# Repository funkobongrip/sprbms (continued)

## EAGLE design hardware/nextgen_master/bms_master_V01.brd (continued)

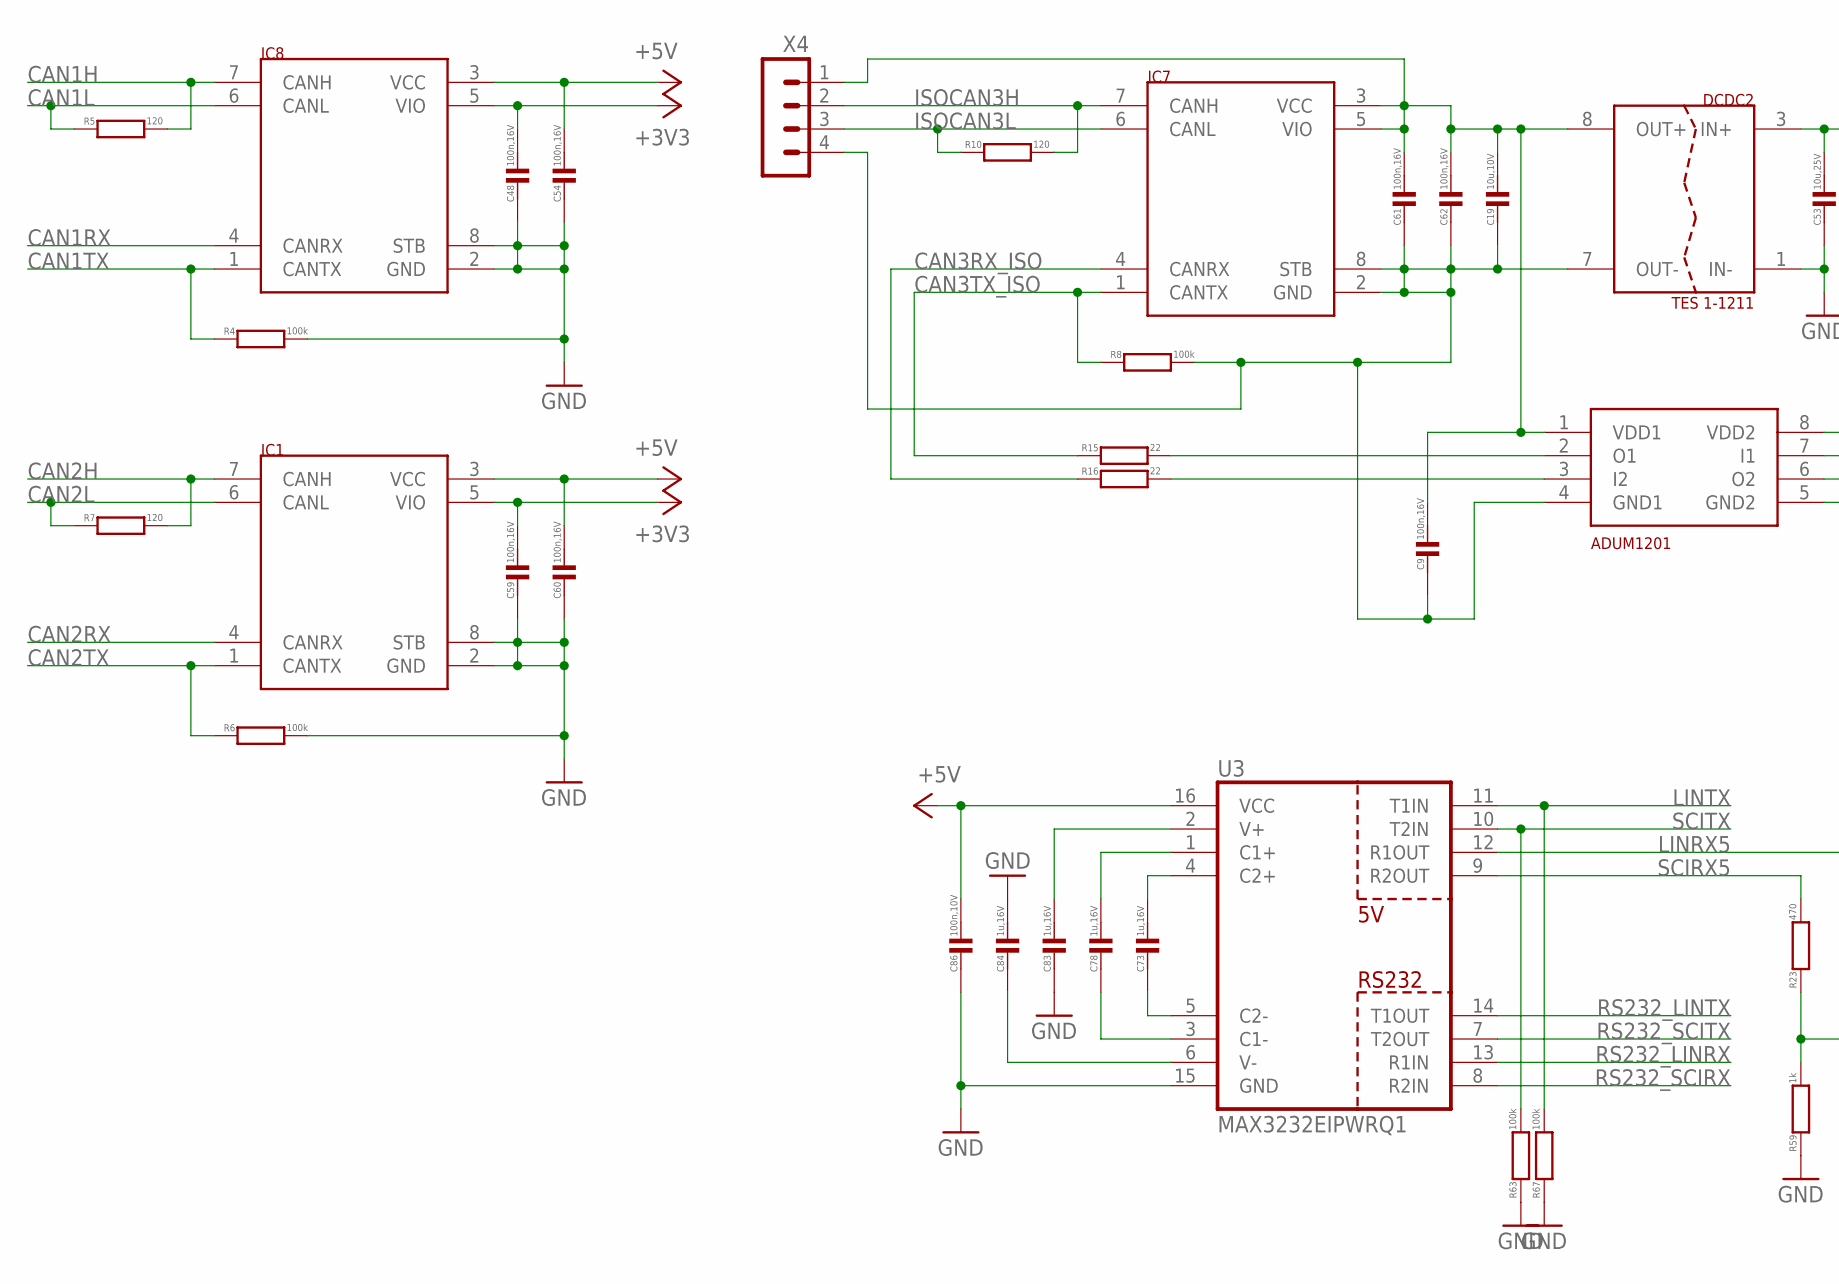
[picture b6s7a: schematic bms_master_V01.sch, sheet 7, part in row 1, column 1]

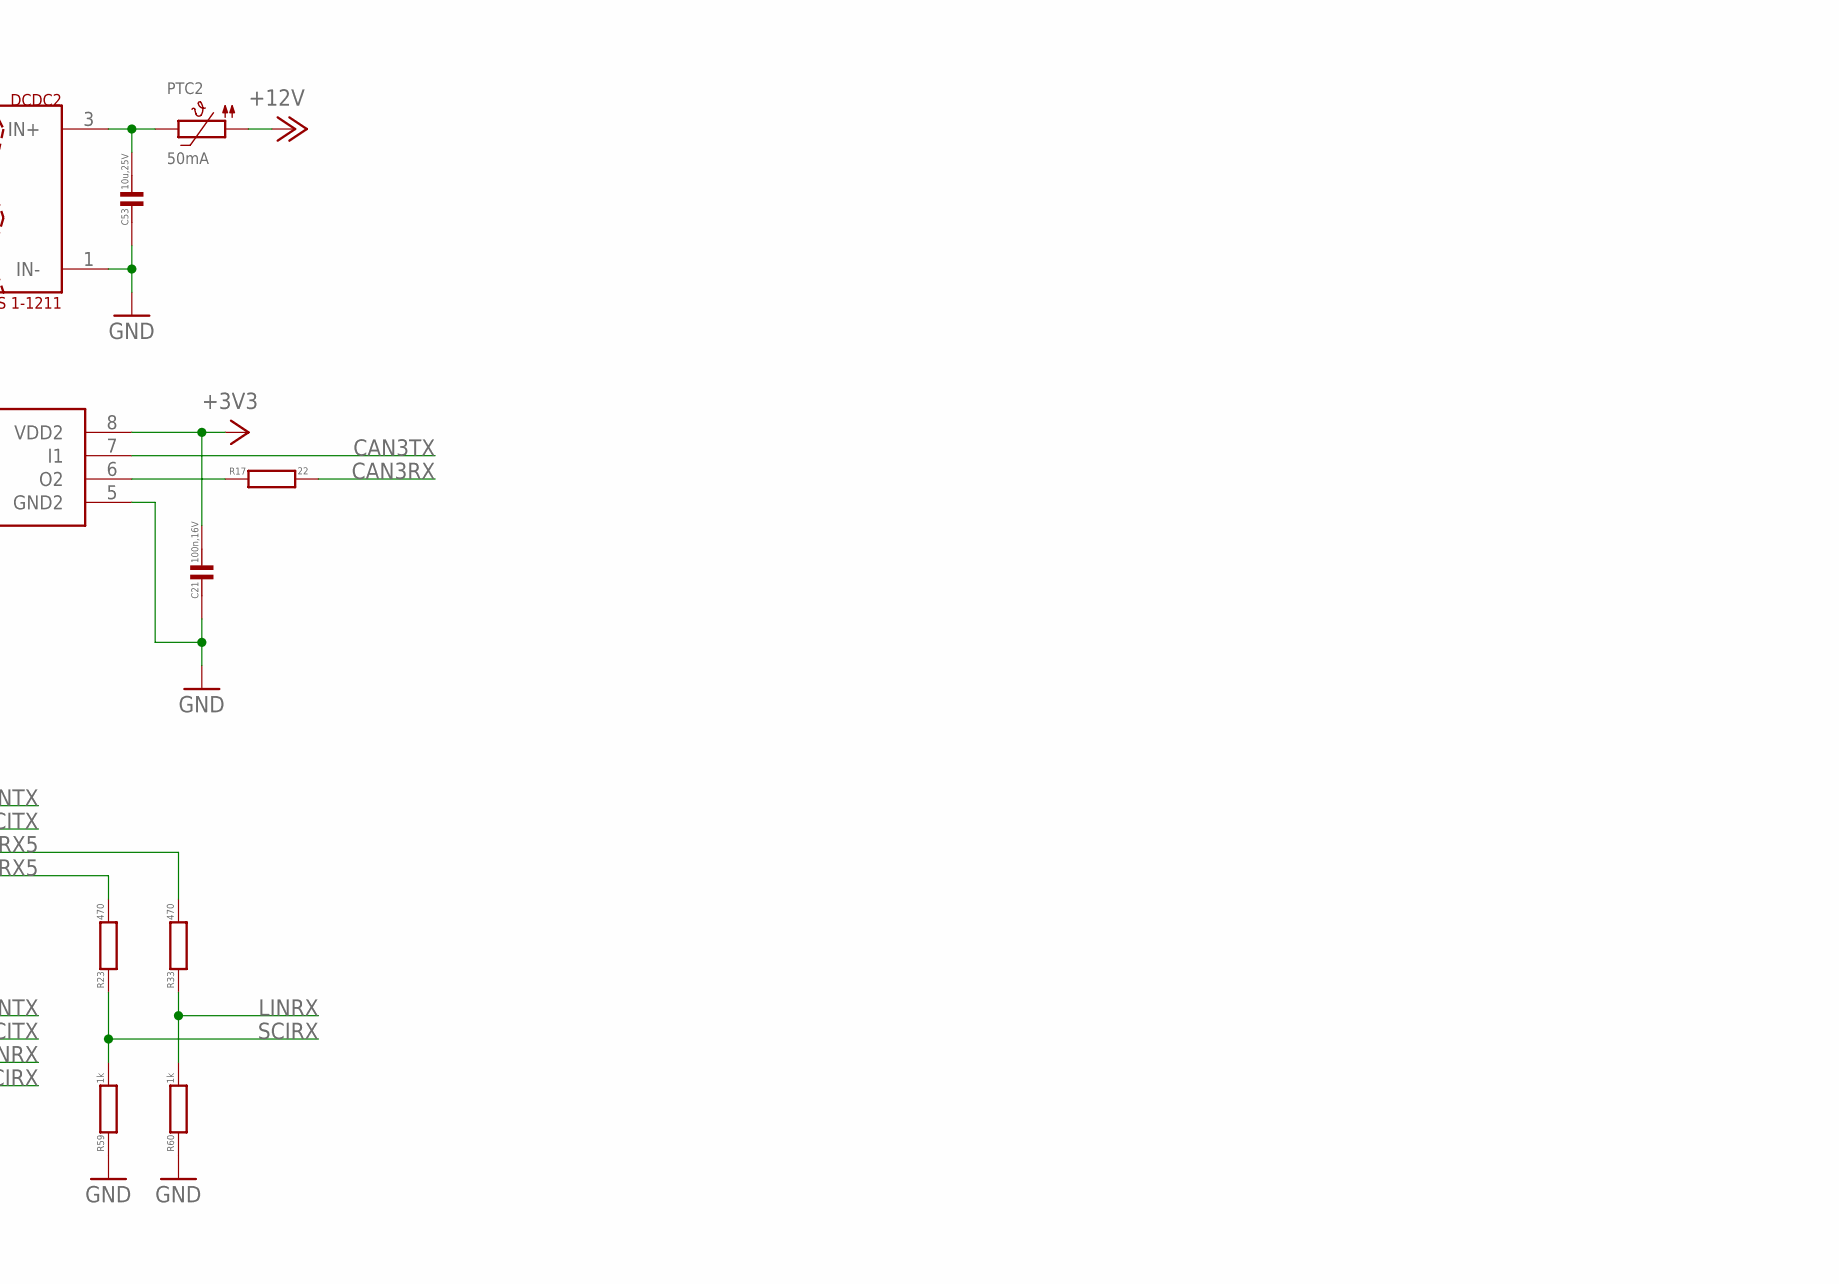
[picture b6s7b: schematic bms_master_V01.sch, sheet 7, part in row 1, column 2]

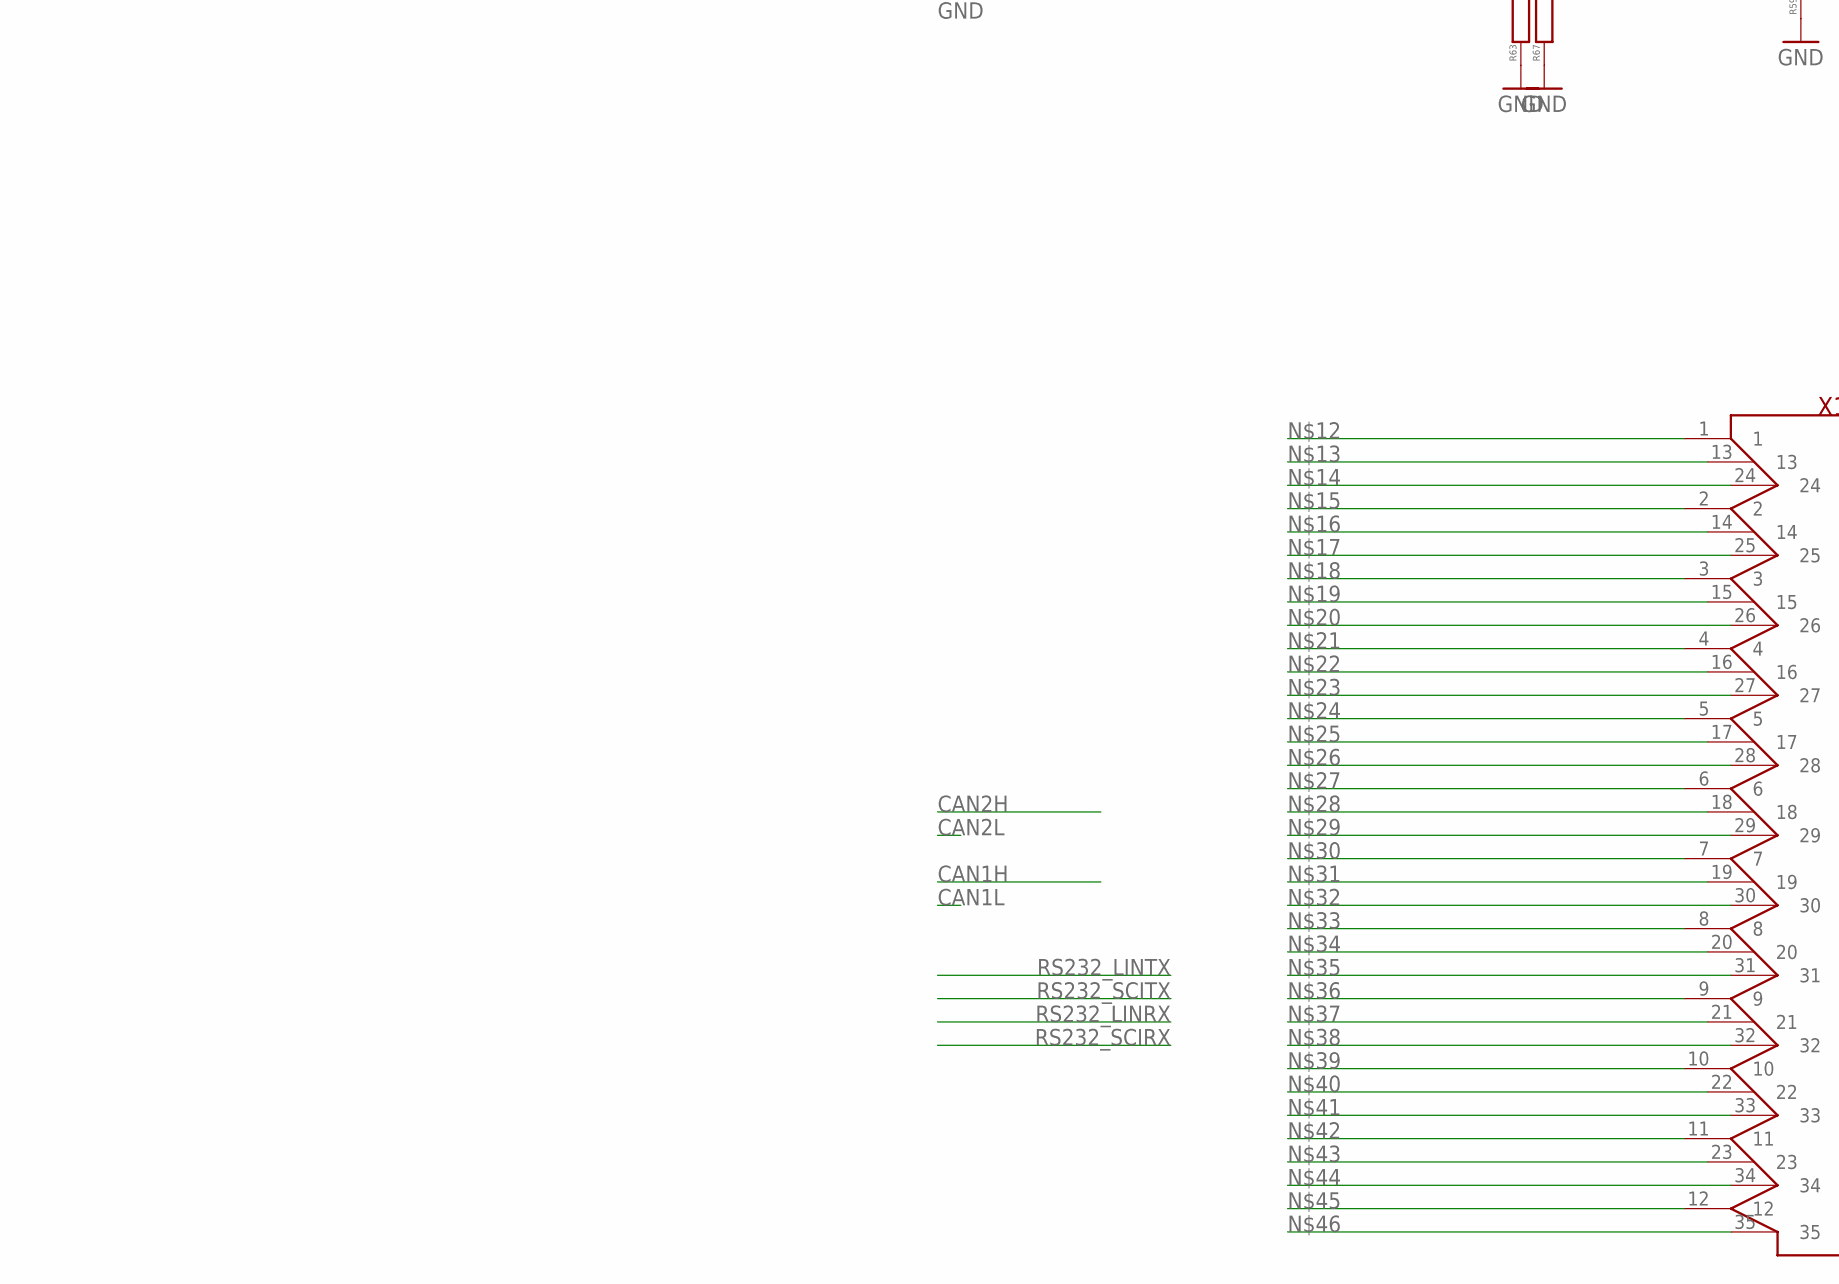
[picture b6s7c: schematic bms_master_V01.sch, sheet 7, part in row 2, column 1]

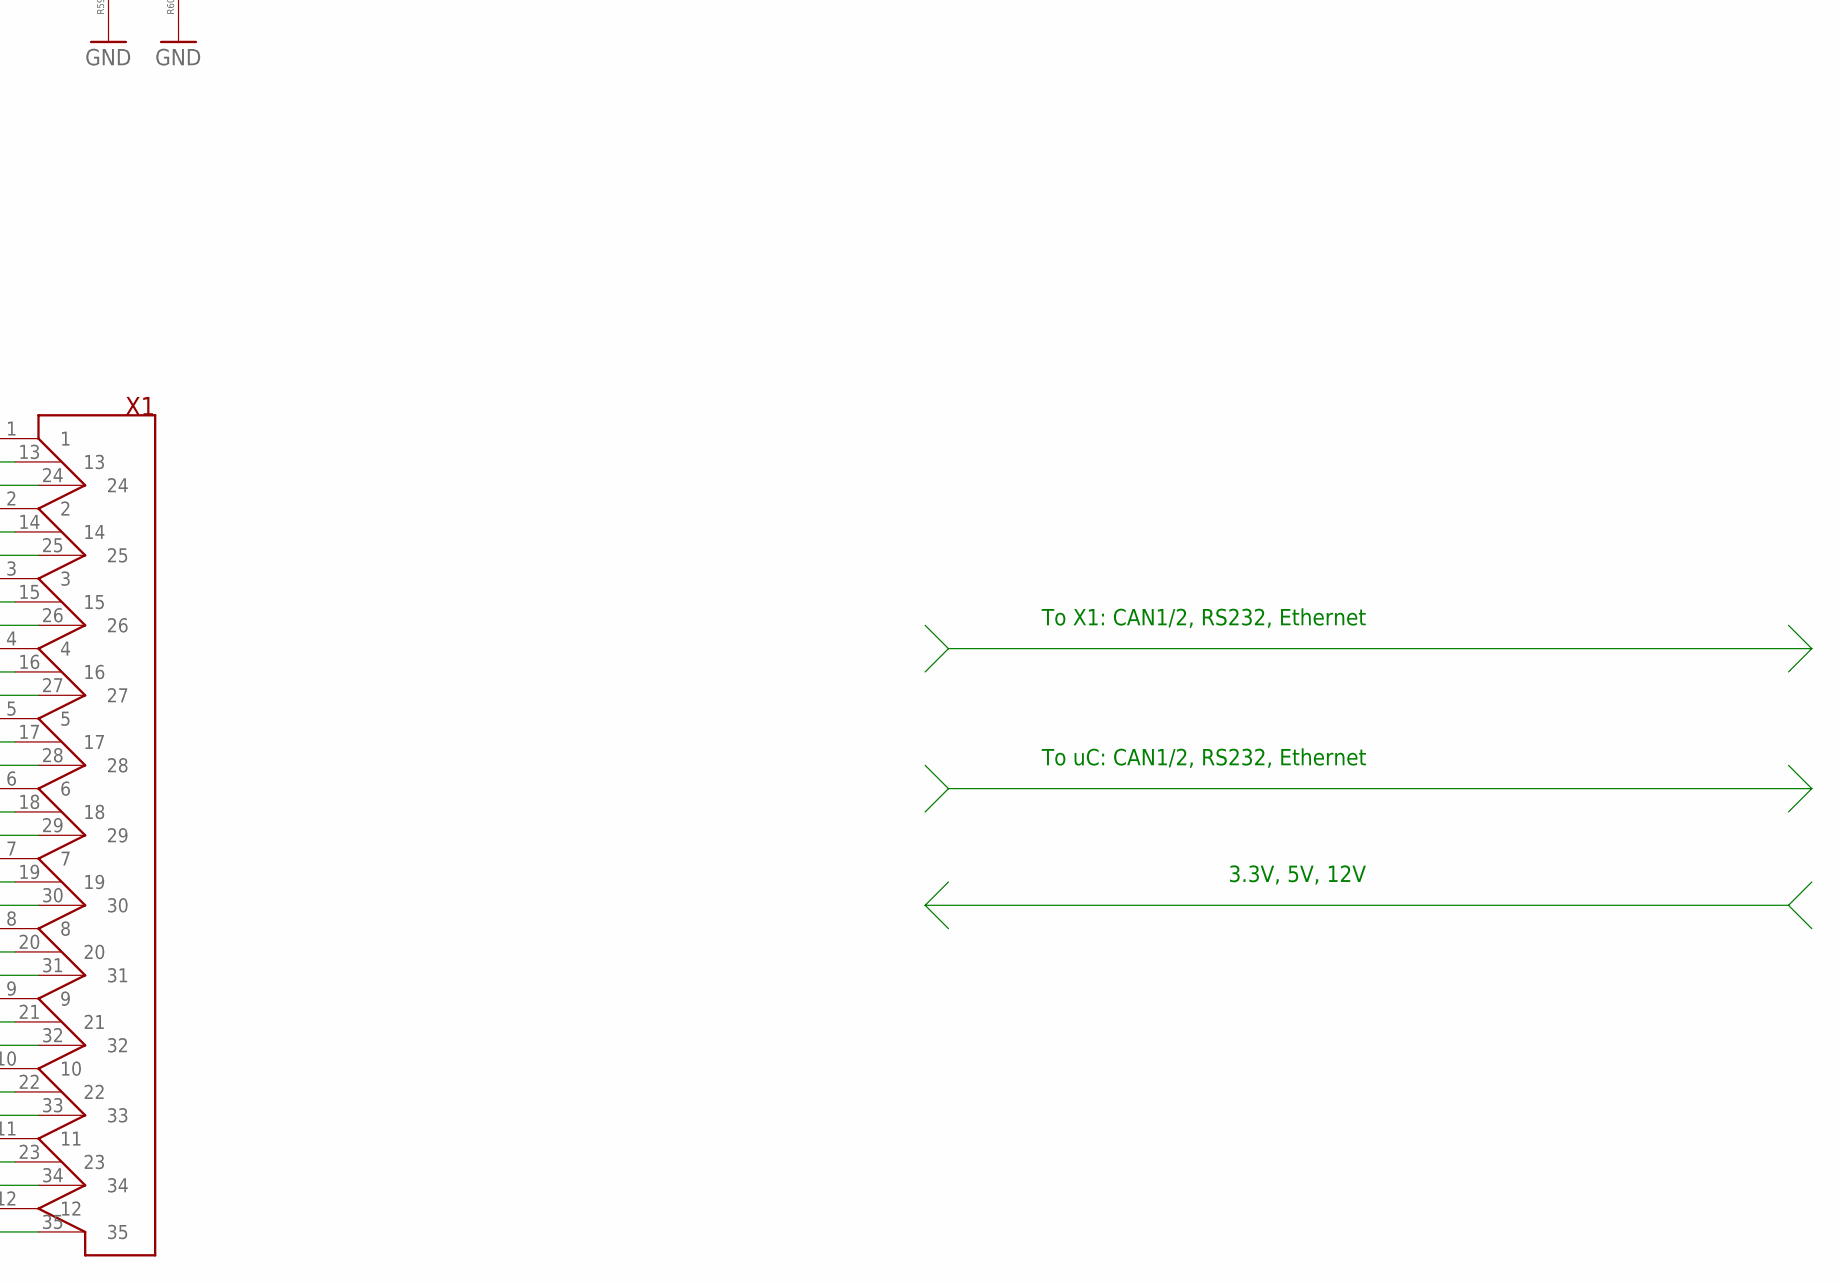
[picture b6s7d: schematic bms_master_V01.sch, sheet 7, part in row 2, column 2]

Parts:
C9, C21, C48, C54, C59, C60, C61, C62: 100n,16V; C0402
C19: 10u,10V; C0603
C53: 10u,25V; C1210
C73, C78, C83, C84: 1u,16V; C0603
C86: 100n,10V; C0402
DCDC2: TES 1-1211; DCDC_SMD_TES1
IC1, IC7, IC8: SN65HVDA540; SO-8
PTC2: 50mA; PTC1210
R4, R6, R8, R63, R67: 100k; R0402
R5, R7, R10: 120; R1206
R15, R16, R17: 22; R1206
R23, R33: 470; R0402
R59, R60: 1k; R0402
U3: MAX3232EIPWRQ1; TSSOP16
U$19: ADUM1201; SO-8
X1: AMPSEAL_35; AMPSEAL_776231-1
X4: HEADER_POS4_43650-0412; 43650-0412

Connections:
+3V3: C21.1, C48.1, C59.1, IC1.5 (VIO), IC8.5 (VIO), U$19.8 (VDD2); also elsewhere on the board
+5V: C54.1, C60.1, C86.1, IC1.3 (VCC), IC8.3 (VCC), U3.16 (VCC); also elsewhere on the board
+12V: PTC2.P$1 (1); also elsewhere on the board
CAN1H: IC8.7 (CANH), R5.2
CAN1L: IC8.6 (CANL), R5.1
CAN1RX: IC8.4 (CANRX); also elsewhere on the board
CAN1TX: IC8.1 (CANTX), R4.1; also elsewhere on the board
CAN2H: IC1.7 (CANH), R7.2
CAN2L: IC1.6 (CANL), R7.1
CAN2RX: IC1.4 (CANRX)
CAN2TX: IC1.1 (CANTX), R6.1; also elsewhere on the board
CAN3RX: R17.2; also elsewhere on the board
CAN3RXR: R17.1, U$19.6 (O2)
CAN3RX_ISO: IC7.4 (CANRX), R16.1
CAN3TX: U$19.7 (I1); also elsewhere on the board
CAN3TX_ISO: IC7.1 (CANTX), R8.1, R15.1
CLV_12V_TES1_FUSED1: C53.1, DCDC2.3 (IN+), PTC2.P$2 (2)
GND: C21.2, C48.2, C53.2, C54.2, C59.2, C60.2, C83.2, C84.1, C86.2, DCDC2.1 (IN-), IC1.2 (GND), IC1.8 (STB), IC8.2 (GND), IC8.8 (STB), R4.2, R6.2, R59.1, R60.1, R63.1, R67.1, U3.15 (GND), U$19.5 (GND2); also elsewhere on the board
ISOCAN3H: IC7.7 (CANH), R10.2, X4.2
ISOCAN3L: IC7.6 (CANL), R10.1, X4.3
ISOCAN_5V: C9.1, C19.1, C61.1, C62.1, DCDC2.8 (OUT+), IC7.3 (VCC), IC7.5 (VIO), U$19.1 (VDD1), X4.1
ISOCAN_GND: C9.2, C19.2, C61.2, C62.2, DCDC2.7 (OUT-), IC7.2 (GND), IC7.8 (STB), R8.2, U$19.4 (GND1), X4.4
LINRX: R33.1, R60.2; also elsewhere on the board
LINRX5: R33.2, U3.12 (R1OUT)
LINTX: R67.2, U3.11 (T1IN); also elsewhere on the board
unnamed: R16.2, U$19.3 (I2)
unnamed: C73.1, U3.4 (C2+)
unnamed: C78.1, U3.1 (C1+)
unnamed: C83.1, U3.2 (V+)
unnamed: C73.2, U3.5 (C2-)
unnamed: R15.2, U$19.2 (O1)
unnamed: C78.2, U3.3 (C1-)
unnamed: C84.2, U3.6 (V-)
RS232_LINRX: U3.13 (R1IN)
RS232_LINTX: U3.14 (T1OUT)
RS232_SCIRX: U3.8 (R2IN)
RS232_SCITX: U3.7 (T2OUT)
SCIRX: R23.1, R59.2; also elsewhere on the board
SCIRX5: R23.2, U3.9 (R2OUT)
SCITX: R63.2, U3.10 (T2IN); also elsewhere on the board

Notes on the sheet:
To X1: CAN1/2, RS232, Ethernet
3.3V, 5V, 12V
To uC: CAN1/2, RS232, Ethernet

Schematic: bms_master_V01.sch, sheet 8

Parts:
C24, C36, C46: 10u,10V; C0603
C87: 1u,10V; C0402
IC11: TMS570LS3137ZWT; S-PBGA-N337
IC18: 74ABT125PW; TSSOP14
L7: 74479774210; WE-PMI_0805
LED3: Y; CHIPLED_0603
R9, R12, R13, R14, R18, R19, R20, R38, R39, R40, R41, R71, R72, R73, R74, R237, R238, R239, R240, R241, R242, R243, R244, R245: 22; R0402
R64: 1k; R0402

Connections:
+3V3: C87.1, IC18.14 (VCC), R64.2; also elsewhere on the board
+3V32: C46.1, L7.1; also elsewhere on the board
AD1EVT: IC11.N19 (AD1EVT/MII_RX_ER/RMII_RX_ER)
AD1_0: IC11.W14 (AD1IN[0])
AD1_1: IC11.V17 (AD1IN[1])
AD1_2: IC11.V18 (AD1IN[2])
AD1_3: IC11.T17 (AD1IN[3])
AD1_4: IC11.U18 (AD1IN[4])
AD1_5: IC11.R17 (AD1IN[5])
AD1_6: IC11.T19 (AD1IN[6])
AD1_7: IC11.V14 (AD1IN[7])
AD1_8/2_8: IC11.P18 (AD1IN[8]/AD2IN[8])
AD1_9/2_9: IC11.W17 (AD1IN[9]/AD2IN[9])
AD1_10/2_10: IC11.U17 (AD1IN[10]/AD2IN[10])
AD1_11/2_11: IC11.U19 (AD1IN[11]/AD2IN[11])
AD1_12/2_12: IC11.T16 (AD1IN[12]/AD2IN[12])
AD1_13/2_13: IC11.T18 (AD1IN[13]/AD2IN[13])
AD1_14/2_14: IC11.R18 (AD1IN[14]/AD2IN[14])
AD1_16/2_0: IC11.V13 (AD1IN[16]/AD2IN[0])
AD1_17/2_1: IC11.U13 (AD1IN[17]/AD2IN[1])
AD1_18/2_2: IC11.U14 (AD1IN[18]/AD2IN[2])
AD1_19/2_3: IC11.U16 (AD1IN[19]/AD2IN[3])
AD1_20/2_4: IC11.U15 (AD1IN[20]/AD2IN[4])
AD1_21/2_5: IC11.T15 (AD1IN[21]/AD2IN[5])
AD1_22/2_6: IC11.R19 (AD1IN[22]/AD2IN[6])
AD1_23/2_7: IC11.R16 (AD1IN[23]/AD2IN[7])
AGND: C24.2, C36.2, C46.2, IC11.V16 (ADREFLO), IC11.V19 (VSSAD), IC11.W16 (VSSAD), IC11.W18 (VSSAD), IC11.W19 (VSSAD); also elsewhere on the board
AREF: C24.1, IC11.V15 (ADREFHI); also elsewhere on the board
AVCC: C36.1, IC11.W15 (VCCAD), L7.2
CAN1RX: IC11.B10 (CAN1RX); also elsewhere on the board
CAN1TX: R19.2; also elsewhere on the board
CAN1TX_R: IC11.A10 (CAN1TX), R19.1
CAN2RX_R: IC11.H1 (CAN2RX)
CAN2TX: R12.2; also elsewhere on the board
CAN2TX_R: IC11.H2 (CAN2TX), R12.1
CAN3RX: IC11.M19 (CAN3RX); also elsewhere on the board
CAN3TX: R14.2; also elsewhere on the board
CAN3TX_R: IC11.M18 (CAN3TX), R14.1
CTRL_AIR+: R242.2; also elsewhere on the board
CTRL_AIR-: R244.2; also elsewhere on the board
CTRL_BRAKEL: R239.2; also elsewhere on the board
CTRL_EXTLOAD1: R237.1; also elsewhere on the board
CTRL_EXTLOAD2: R238.1; also elsewhere on the board
CTRL_PRECH: R241.2; also elsewhere on the board
CTRL_PUMP: R243.2; also elsewhere on the board
CTRL_RTDS: R240.2; also elsewhere on the board
CTRL_SAFE_AIR+: IC11.H3 (GIOA[6]/N2HET2[4]); also elsewhere on the board
CTRL_SAFE_AIR-: IC11.M1 (GIOA[7]/N2HET2[6]); also elsewhere on the board
DIAG: IC11.P19 (AD1IN[15]/AD2IN[15]); also elsewhere on the board
ENDRV: IC18.9 (I); also elsewhere on the board
ENLSDRV: R245.2; also elsewhere on the board
FRAYRX1: IC11.A15 (FRAYRX1)
FRAYRX2: IC11.B15 (FRAYTX1)
FRAYTX1: IC11.B16 (FRAYTXEN1)
FRAYTX2: IC11.A8 (FRAYRX2)
FRAYTXEN1: IC11.B8 (FRAYTX2)
FRAYTXEN2: IC11.B9 (FRAYTXEN2)
GND: C87.2, IC18.1 (OE), IC18.4 (OE), IC18.7 (GND), IC18.10 (OE), IC18.13 (OE); also elsewhere on the board
HV_!CS: R20.1; also elsewhere on the board
HV_MISO: IC11.D2 (SPI2SOMI[0]); also elsewhere on the board
HV_SCK: R18.1; also elsewhere on the board
LED1A2: LED3.A, R64.1
LINRX: IC11.A7 (LINRX); also elsewhere on the board
LINTX: R13.1; also elsewhere on the board
unnamed: IC11.B7 (LINTX), R13.2
unnamed: IC11.N2 (N2HET1[13]/SCITX), R9.2
unnamed: IC11.E2 (SPI2CLK), R18.2
unnamed: IC11.N3 (SPI2NCS[0]), R20.2
unnamed: IC11.G1 (GIOB[4]), IC18.11 (O)
unnamed: IC11.B3 (N2HET1[22]), R237.2
unnamed: IC11.J4 (N2HET1[23]), R238.2
unnamed: IC11.F2 (GIOB[2]), R244.1
unnamed: IC11.E1 (GIOA[3]/N2HET2[2]), R243.1
unnamed: IC11.C2 (GIOA[1]), R242.1
unnamed: IC11.A5 (GIOA[0]), R241.1
unnamed: IC11.J17 (N2HET1[31]), R240.1
unnamed: IC11.B11 (N2HET1[30]/MII_RX_DV), R239.1
unnamed: IC11.W10 (GIOB[3]), R245.1
unnamed: IC11.M3 (N2HET1[25]), LED3.C
unnamed: IC11.B5 (GIOA[5]/EXTCLKIN/N2HET1_PIN_NDIS), IC18.8 (O)
unnamed: IC11.C1 (GIOA[2]/N2HET2[0]), IC18.6 (O)
unnamed: IC11.A3 (N2HET1[29]), IC18.3 (O)
OVER60V: IC18.2 (I); also elsewhere on the board
PRECH_CURRENT: IC18.5 (I); also elsewhere on the board
RELAY_CLOSED: IC18.12 (I); also elsewhere on the board
RTC_!CS: R73.1; also elsewhere on the board
RTC_!CSR1: IC11.F3 (MIBSPI1NCS[1]/N2HET1[17]/MII_COL), R73.2
RTC_!INT: IC11.J3 (MIBSPI1NCS[3]/N2HET1[21]); also elsewhere on the board
SCIRX: IC11.W3 (N2HET1[6]/SCIRX); also elsewhere on the board
SCITX: R9.1; also elsewhere on the board
SCL: IC11.C3 (MIBSPI3NCS[3]/I2C_SCL/N2HET1[29]); also elsewhere on the board
SDA: IC11.B2 (MIBSPI3NCS[2]/I2C_SDA/N2HET1[27]); also elsewhere on the board
SD_!CS: R39.1; also elsewhere on the board
SD_!CS_R: IC11.V5 (MIBSPI3NCS[1]/N2HET1[25]/MDCLK), R39.2
SD_CD: IC11.T1 (N2HET1[7]/N2HET2[14]); also elsewhere on the board
SD_CLK: R38.1; also elsewhere on the board
SD_CLK_R: IC11.V9 (MIBSPI3CLK), R38.2
SD_EN: R41.1; also elsewhere on the board
SD_EN_R: IC11.W9 (MIBSPI3NENA/MIBSPI3NCS[5]/N2HET1[31]), R41.2
SD_MISO: IC11.V8 (MIBSPI3SOMI[0]); also elsewhere on the board
SD_MOSI: R40.1; also elsewhere on the board
SD_MOSI_R: IC11.W8 (MIBSPI3SIMO[0]), R40.2
SLAVE_!CS: IC11.E19 (MIBSPI5NCS[0]/DMM_DATA[5])
SLAVE_!ENA: IC11.H18 (MIBSPI5NENA/DMM_DATA[7]/MII_RXD[3])
SLAVE_CLK: IC11.H19 (MIBSPI5CLK/DMM_DATA[4]/MII_TXEN/RMII_TX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)
SLAVE_MISO: IC11.E16 (MIBSPI5SIMO[1]/DMM_DATA[9])
SLAVE_MOSI: IC11.J19 (MIBSPI5SIMO[0]/DMM_DATA[8]/MII_TXD[1]/R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)
STATUS_AIR+: IC11.K2 (GIOB[1])
STATUS_AIR-: IC11.A6 (GIOA[4])
STATUS_BMS: IC11.F1 (GIOB[7]); also elsewhere on the board
STATUS_BSPD: IC11.G2 (GIOB[5]); also elsewhere on the board
STATUS_IMD: IC11.J2 (GIOB[6]); also elsewhere on the board
STATUS_PRECH: IC11.M2 (GIOB[0])
TPS_!CS: R72.1; also elsewhere on the board
TPS_!CSR1: IC11.R2 (MIBSPI1NCS[0]/MIBSPI1SOMI[1]/MII_TXD[2]), R72.2
TPS_MISO: IC11.G18 (MIBSPI1SOMI[0]); also elsewhere on the board
TPS_MOSI: R74.1; also elsewhere on the board
TPS_MOSIR1: IC11.F19 (MIBSPI1SIMO[0]), R74.2
TPS_SCK: R71.1; also elsewhere on the board
TPS_SCKR1: IC11.F18 (MIBSPI1CLK), R71.2

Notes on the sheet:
TODO

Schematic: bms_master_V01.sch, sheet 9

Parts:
0,5SDELAY: 0.5s_Delay; B1,27
5KW: FINDER-30.22
5KW-CHECK: LM321MF; SOT23-5
5KW-CHECKK: 5KW_Check; B1,27
5KW-REF: 5KW_REF; B1,27
AIR+: 66200421122
AIR-: 66200421122
BMS: 66200421122
BRAKE1: BRAKE; B1,27
BRAKEREF1: BRAKE_REF; B1,27
BREMSPEDAL-CHECK: LM321MF; SOT23-5
C124, C125, C126, C127, C131, C132, C147, C148, C165, C166, C167: 100nF; C0603
C128, C130, C157, C158: DNP; C0603
C129: 47uF; C1206
C149: 10nF; C0603
C150: 100uF; C1206K
C151: 33uF; C1206
C152: 10uF; C0603
C159: 100n; C0603
C164: 10uF; C1206K
C178, C191, C194, C195, C196: 450BXF47M18X20; E7,5-18
C179: MAL219612105E3; E5-13
C180: CC0603ZRY5V7BB105; C0603
C181, C192: 10u,50V; C1206
C182: 06036D475KAT2A; C0603
C183, C184: VY1472M63Y5UG63V0; YC10B5
C185, C186: DEBF33A103ZA2B; C050-040X10
C188, C197: CKG57NX7T2W225M500JH; C2220K
C189, C193: 100n; C1206
C190, C198: EMK325ABJ107MM-T; C1210
CA_0,92V: 1k5_5KW_REF; S64W
D25, D26: DIODE-SOD323-R; SOD323-R
D31: DSOD323; SOD323
D37: DIODE-SOD323-W; SOD323-W
D38: DIODE-SOD123; SOD123
D39: 10V; DO-214AC
D40: 10V, DNP; DO-214AC
D41: < 600V; DO-214AC
F6: 0477005.MXP; SHK20L
F7: 0034.3130; SHK20L
GND, GND174: GND; B1,27
HARD-BRAKE: HARD_BRAKE; B1,27
HOT_HV+: 64900211122
HOT_HV-: 64900211122
IC21: NE555D; SO08
IC22, IC27: 74AHC1GU04DBV; SOT23-5
IC25: 74AHC1G08DBV; SOT23-5
IC26: SN74LVC1G175DBV; SOT23-6
IC31: LTC1440; SO08
K2: Energymeter_Connector; 66200211122
K3: Discharge_Connector; 66200421122
KOMPERATOR: LM321MF; SOT23-5
LED7: LEDCHIPLED_1206; CHIPLED_1206
LEM-CONNECTOR: LEM_Connector; 66200411122
LEM-OUT: LEMC_OUT; B1,27
MOSFET: MOSFET; B1,27
NE555-IN: NE555_IN; B1,27
NE555-OUT: NE555_OUT; B1,27
PRECHARGE1: 66200211122
R132: 10k_BRAKE_REF; S64W
R133, R141, R149, R154, R157, R158: 1k; R0603
R142, R150: DNP; R0603
R143: 10k; S64W
R144, R152, R159: 470; R0603
R145: 1k5; R0603
R146, R181: 4k7; R0603
R153: 10; R0603
R155, R160, R185, R186, R188: 100k; R0603
R156: 470k; R0603
R195: 100k; S64W
R196: 1M; R0603
R197, R221: 10k; R0603
R214: MS2222103
R215: 220; R0603
R216: 560; R0603
R217: 1k; R1206
R218, R230, R233: 50k; WSC2515
R219, R229: 1M; WSC2515
R220: 25k; R1206
R222: 430 nom; R0603
R223: 2.4M nom; R0603
R224, R225: 3223W-1-203; 3223W
R228: 120; R0603
R231: 100k; R1206
R232: DNP; R1206
R234: 0, DNP; R1210
R235: 500; R1206W
T1: NMOSSOT23; SOT-23
T2: IRFPS43N; TO247BV
TP1, TP2, TP3, TP4, TP5, TP6, TP7, TP9, TP10, TP11, TP12, TP13: TPB2,54; B2,54
TP8: TPB1,27; B1,27
U$26: AMSEAL23RW; AMPSEAL23RW
U$27: VICORPOWER_V375B12C300BL2
U$28: ASSR-5211; DIL06
U$29: LS220
UND: 74AHCT1G08DBV; SOT23-5
X7: AMPSEAL_35; AMPSEAL_776231-1
Z-DIODE1: 5,1V; SOD323-R

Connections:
0,5SDELAY: 0,5SDELAY.TP, C151.1, KOMPERATOR.3 (-IN), R143.E, R144.1
3.6V_FROM_BATTERY: D37.A, U$26.10
5KW-CHECK: 5KW-CHECK.4 (OUT), 5KW-CHECKK.TP, R185.1, UND.2 (I1)
5KWOP-: 5KW-CHECK.1 (+IN), 5KW-REF.TP, C126.2, CA_0,92V.S, R181.2, R185.2
10V: C181.1, C193.1, D39.C, IC31.7 (V+), R218.1, R232.1, TP6.TP
12V_TO_LVMS: F7.2A, R235.2, U$26.3, U$26.11, U$26.18
+5V: 5KW-CHECK.5 (V+), BREMSPEDAL-CHECK.5 (V+), C125.1, C127.1, C129.2, C131.1, C132.1, C147.2, C148.1, C159.2, C165.2, C166.2, C167.2, IC21.8 (V+), IC22.5 (VCC), IC25.5 (VCC), IC26.3 (D1), IC26.5 (VCC), IC27.5 (VCC), KOMPERATOR.5 (V+), LEM-CONNECTOR.2, R133.1, R145.2, R154.2, R155.1, R157.2, R181.1, R195.A, R197.1, UND.5 (VCC); also elsewhere on the board
AND_5KW: IC22.4 (O), IC25.1 (I0)
AND_TIMER: IC25.2 (I1), IC27.4 (O)
BEHIND_HVMS: K3.1, K3.2, X7.7
BMS_STATUS: U$26.13
BRAKE: R156.2, R158.2, X7.29
BRAKE1OP+: BRAKE1.TP, BREMSPEDAL-CHECK.1 (+IN), C124.1, R158.1, R186.2, Z-DIODE1.C
BRAKE1OP-: BRAKEREF1.TP, BREMSPEDAL-CHECK.3 (-IN), C124.2, R132.S, R133.2
CANH: X7.6
CANH1: BMS.1, U$26.12
CANL: X7.17
CANL1: BMS.2, U$26.4
CAR+12VIN: BMS.4, R216.1, U$26.6
CHAIN-IN: X7.30
CHAIN-IN1: U$26.7
CHAIN-OUT1: U$26.8
CHAIN_RESET: X7.27
CTRL_BRAKEL: X7.22; also elsewhere on the board
CTRL_CHARGE: X7.16
CTRL_MAIR: X7.14
CTRL_PAIR: X7.15
CTRL_PUMP: X7.23; also elsewhere on the board
CTRL_RTDS: X7.13; also elsewhere on the board
CURRENT_20A: 5KW-CHECK.3 (-IN), C126.1, C130.2, LEM-OUT.TP, R149.1, R150.2
CURRENT_UC: C128.2, R141.1, R142.2
DCDC+: C178.+, C184.1, C188.1, C194.+, C195.+, C197.1, R214.2, TP10.TP, U$27.+IN (1_+IN)
DCDC-: C178.-, C183.2, C188.2, C194.-, C195.-, C197.2, T2.D (D1), U$27.-IN (4_-IN)
DCDCOUT+: C186.1, C190.1, C198.1, F7.1A, TP11.TP, U$27.+OUT (9_+OUT), U$27.+S (8_+S)
DELAYOP+: KOMPERATOR.1 (+IN), R145.1, R146.2, R188.2, TP8.TP
DISCHARGE: IC21.7 (DIS), R159.2
GATE: R152.2, R153.1, T1.3 (G)
GATE1: C189.1, D40.C, R217.2, R231.2, R232.2, T2.G (G1), TP9.TP
GND: 5KW-CHECK.2 (V-), BREMSPEDAL-CHECK.2 (V-), C125.2, C127.2, C128.1, C129.1, C130.1, C131.2, C132.2, C147.1, C148.2, C149.2, C150.2, C151.2, C152.2, C157.1, C158.1, C159.1, C164.2, C165.1, C166.1, C167.1, CA_0,92V.E, GND.TP, GND174.TP, IC21.1 (GND), IC22.3 (GND), IC25.3 (GND), IC26.2 (GND), IC27.3 (GND), K2.2, KOMPERATOR.2 (V-), LEM-CONNECTOR.3, R132.E, R142.1, R146.1, R150.1, R152.1, R156.1, R160.1, R196.2, T1.2 (S), UND.3 (GND), X7.5, Z-DIODE1.A; also elsewhere on the board
GND_TO_DSPACE: BMS.3, U$26.5
GROUND: AIR+.3, AIR-.3, C179.-, C185.2, C190.2, C198.2, LED7.C, R234.2, TP13.TP, U$26.1, U$26.9, U$26.16, U$27.-OUT (5_-OUT), U$27.-S (6_-S), U$28.2 (2-K)
HARD-BRAKE: BREMSPEDAL-CHECK.4 (OUT), HARD-BRAKE.TP, R186.1, UND.1 (I0)
HOT_BF_VH+: F6.1A, HOT_HV+.1, HOT_HV+.2
HV+: C191.+, C196.+, D41.C, F6.2A, R214.1, TP1.TP, U$28.4 (4-DC)
HV+MR: R219.2, R229.1
HV+SW: D41.A, R229.2, R233.2, TP2.TP, U$28.6 (6+)
HV+SW1: R230.2, R233.1
HV+SW2: R218.2, R230.1
HV-1: C180.2, C181.2, C189.2, C191.-, C192.2, C193.2, C196.-, D39.A, D40.A, HOT_HV-.1, HOT_HV-.2, IC31.1 (GND), IC31.2 (V-), R223.1, R224.1 (A), R224.2 (S), R231.1, T2.S (S1)
HYST: IC31.5 (HYST), R223.2, R225.3 (E)
IN+: C192.1, IC31.3 (IN+), R219.1, R220.2, TP3.TP
LVMS_IN: C182.2, D38.C, R215.1, TP7.TP, U$26.19
LVMS_OUT: C179.+, D37.C, U$26.2
M_BRAKEL: X7.34
M_PUMP: X7.35
unnamed: D25.A, R144.2
unnamed: C157.2, LEM-CONNECTOR.4, R149.2
unnamed: C158.2, LEM-CONNECTOR.1, R141.2
unnamed: IC26.4 (Q1), IC27.2 (I)
unnamed: D31.2 (A), IC26.1 (CLK), R197.2
unnamed: D38.A, R216.2
unnamed: R220.1, R224.3 (E), TP4.TP
unnamed: C182.1, R215.2, R228.1
unnamed: LED7.A, R235.1
NE555-CV: C149.1, IC21.5 (CV)
NE555-IN: IC21.2 (TR), KOMPERATOR.4 (OUT), NE555-IN.TP, R154.1, R188.1
NE555-OUT: IC21.3 (Q), IC22.2 (I), NE555-OUT.TP
NE555-RESET: C152.1, IC21.4 (R), R157.1, R160.2
NOT-OUT: IC25.4 (O), R153.2
OPTOA: R228.2, TP12.TP, U$28.1 (1-A)
OUT: IC31.8 (OUT), R217.1
P_BRAKEL: X7.11
P_CHARGE: K3.3, K3.4, X7.4
P_MAIR: X7.2
P_PAIR: X7.3
P_PUMP: X7.12
P_RTDS: X7.1
REF: IC31.4 (IN-), IC31.6 (REF), R221.2, R222.2
REFF: C180.1, R222.1
REFR: R221.1, R225.1 (A), R225.2 (S), TP5.TP
RELAY-M: AIR-.1, U$26.21
RELAY-P: AIR+.2, U$26.23
RELAY/S-C: PRECHARGE1.2, U$26.15
RELAYS-M: AIR-.4, U$26.20
RELAYS-P: AIR+.4, U$26.14
RGND: X7.24
SL: C164.1, IC26.6 (CLR), R195.S, R196.1
SNUBHV+: C184.2, U$27.+IN/Y2
SNUBHV-: C183.1, U$27.-IN/Y2
SNUBLV+: C186.2, U$27.+OUT/Y2
SNUBLV-: C185.1, R234.1, U$27.-OUT/Y2
SOURCE: 5KW.A2 (2), D26.A, D31.1 (C), MOSFET.TP, T1.1 (D)
SPARE1: X7.32
SPARE2: X7.18
SPARE3: X7.9
SPARE4: X7.21
SPARE5: X7.10
SPARE6: X7.33
THRESHOLD: C150.1, IC21.6 (THR), R155.2, R159.1
TSAL: X7.28
TSAL_OVR1: X7.19
TSAL_OVR2: X7.20
TSAL_OVR3: X7.31
UND-OUT: D25.C, R143.S, UND.4 (O)
VIN: 5KW.A1 (1), D26.C, K2.1, X7.8; also elsewhere on the board
VINRELAY: X7.26
VRELAY: X7.25
VRELAY1: AIR+.1, AIR-.2, PRECHARGE1.1, U$26.22

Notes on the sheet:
Vout=VC/5 (G*Ip+2.5)
Vout=1,096V
Current_UC
Vout= 5V/5*(0,1V/A*(-14,07A)+2,5)
Als Test wird Teststecker gebaut
Strom muss entgegengesetzt des Pfeiles auf dem Datenblatt durch den LEM-Sensor fließen, weil wir den 420A Bereich brauchen, deswegen ein negatives Vorzeichen bei Ip.
CURRENT_20A
LEM-Supply
Ip=5000W/(96*3,7V)=14,07A
LEM DHAB S/44
Funktion: Wenn Lem-Wandler einen Strom von größer 15,78A misst schaltet der Komperator auf High, weil mehr als 5KW aus dem Motor gezogen werden bei Nominaler-Spannung
Funktion: Bei harter Bremsung (kurz bevor die Reifen sich nicht mehr drehen) kommt High am Ausgang des ODER-Gatters
Funktion: Bei mehr als 5KW und harter Bremsung soll nach 500ms die Notauskette aufgehen.
Funktion Komperator: Bei mehr als 5KW und harter Bremsung soll nach 400ms LOW am Ausgang des Komperators kommen.
Funktion NE555: Nach einem LOW-Impuls vom Komperator, hat der Ausgang vom NE555 für ca. 10Sekunden High und durch das NICHT-Gatter High und sperrt den MOSFET für 10Sekunden
Abfolge Einschalten: CLR negativ -> Q negativ In dieser Zeit erfolgt Einschalten durch NE555 CLK wird über MOSFET nach Low gezogen D1 ist High CLR nach Zeit x auch high Durch öffnen Seitens der 5kW Erkennung gibt es Low->High Flanke an CLK Ausgang geht auf High -> Kann nie wieder zurückgesetzt werd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
VRELAY - 12V Steuerspannung für die AIR-Spulen und die Precharge-Spule nach TSMS Die beiden AIRs und Das Precharge-Relais werden seperat von dSpace angesteuert
VRELAY: Leitung zu den Erregerspulen AIR+, AIR-, Charge RELAY-X: Leitungen an den Spulenkontakten RELAYS-X: Status des entsprechenden Relays
1. LVMS_IN + 2. LVMS-OUT + 3. 12V_TO_LVMS + 14A 4. CAR+12VIN + 5. GROUND + 14A 6. 3.6V_FROM_BATTERY + 7. VRELAY + 8. RELAY-M + 9. RELAYS-M + 10. RELAY-P + 11. RELAYS-P + 12. RELAY/S-C + 13. GND_TO_DSPACE + 14. BMS-STATUS + 15. CANH + 16. CANL + 17. CHAIN-IN + 18. CHAIN-OUT +
Status-LED an LVMS_IN Kontakt zu HMI

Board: 4 copper layers, 564 parts (36 on the bottom side), 341 nets, no tracks yet.
